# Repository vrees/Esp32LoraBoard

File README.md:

# Esp32LoraBoard
ESP32 board including Lora RFM95 module optimized for low power deep sleep operation. 

## Features:
* works with single LiFePo battery
* external peripheral (i2c bus, Oled, measurement resistors) can be switxched off by FET transistors
* Open Source. Feel free to modify in KiCad and create your own boards
* I2C bus is decoubled be levelshifters
* optional power supply circuit (solder if you don't want do use LiFePo battery supply)
* optional Rotary Encoder 
* there is no UART chip (like CP2104) onboard in order to save power. Board can be programmed by using a simple external USB-to-UART converter (5 Pins: Ground, RX, TX RTS, DTR)

[PCB](../master/kicad/images_V1.1/Esp32LoraBoard_Kicad_PCB_V1.1.png)

### Power consumption

#### Power on and idle 

After PowerOn without sending any Lora data

| Mode              | Current usage |
| ----------------- |:-------------:|
| Normal operation  | 28 mA         |

#### Deep Sleep 

Switched off all peripheral components and shutdown the RFM95W lora chip.

| Mode              | Current usage |
| ----------------- |:-------------:|
| Deep Sleep        | 26 uA         |

### Get Started

* Clone this project and open in platformio.

* Clone ttn-esp32 into lib subdir. Switch to branch dev to get it running. More info see https://github.com/manuelbl/ttn-esp32

* Following has to be changed under in ./lib/ttn-esp32 
Change following:

__src/lmic/config.h__
#define USE_ORIGINAL_AES

__src/aes/lmic_aes.c__
line 263:  u4_t t0, t1=0, t2, t3;

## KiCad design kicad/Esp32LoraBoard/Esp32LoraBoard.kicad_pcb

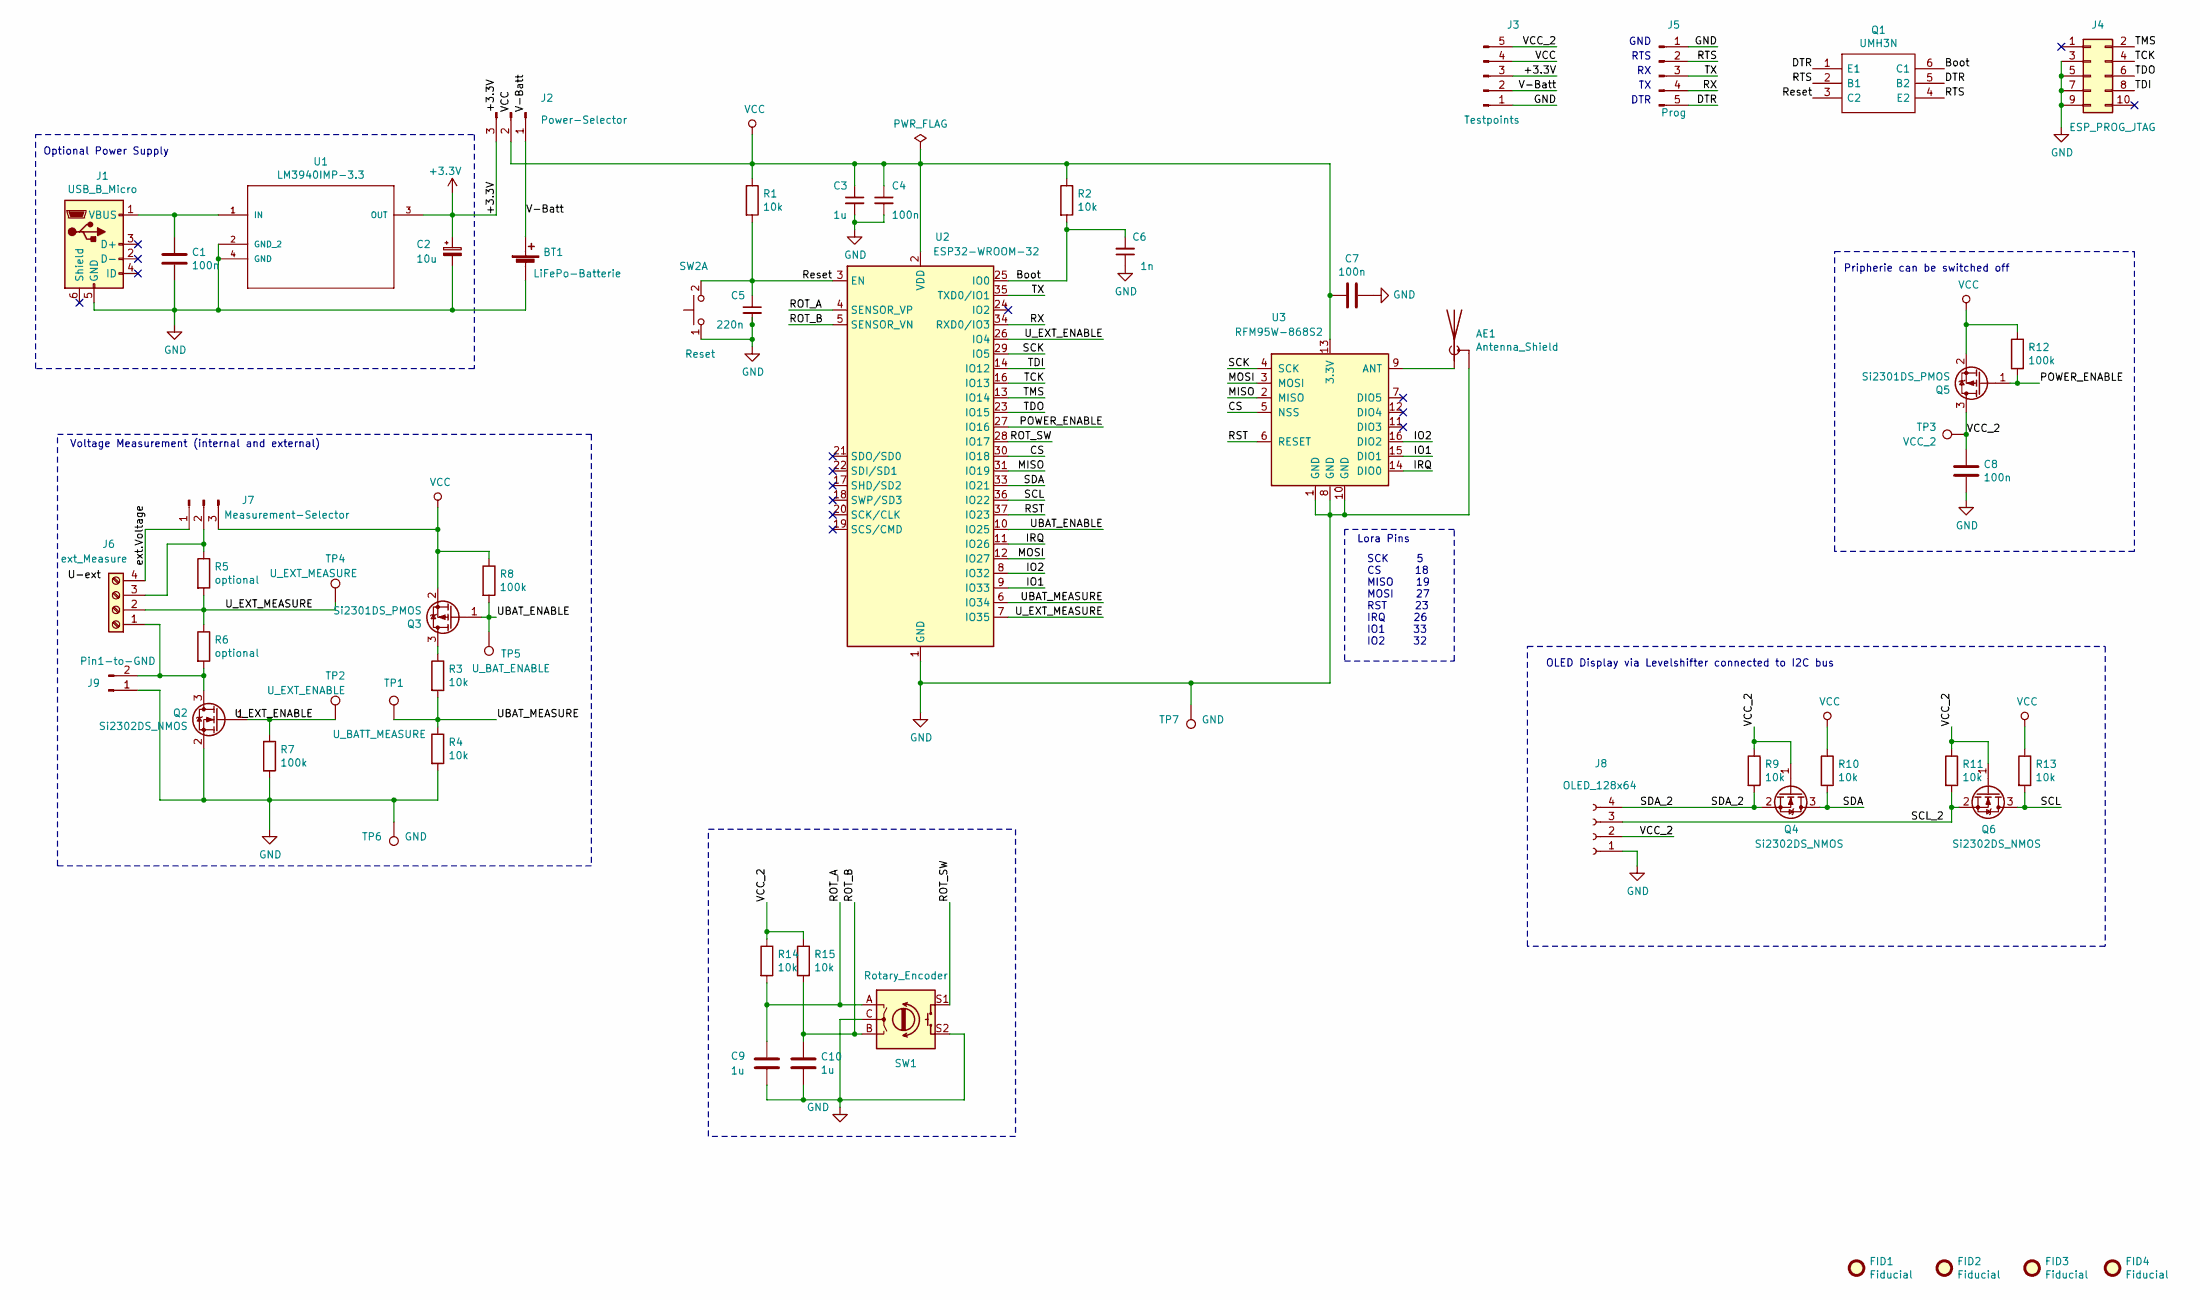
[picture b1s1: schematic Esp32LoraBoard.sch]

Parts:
AE1: Antenna_Shield; SMA_Samtec_SMA-J-P-H-ST-EM1_EdgeMount
BT1: LiFePo-Batterie; PhoenixContact_MSTBVA_2,5_2-G-5,08_1x02_P5.08mm_Vertical
C1, C4, C7, C8: 100n; C_1206_3216Metric_Pad1.42x1.75mm_HandSolder
C2: 10u; C_1206_3216Metric_Pad1.42x1.75mm_HandSolder
C3, C9, C10: 1u; C_1206_3216Metric_Pad1.42x1.75mm_HandSolder
C5: 220n; C_1206_3216Metric_Pad1.42x1.75mm_HandSolder
C6: 1n; C_1206_3216Metric_Pad1.42x1.75mm_HandSolder
FID1, FID2, FID3, FID4: Fiducial; Fiducial_0.75mm_Mask1.5mm
J1: USB_B_Micro; USB_Micro-B_GCT_USB3076-30-A
J2: Power-Selector; PinHeader_1x03_P2.54mm_Vertical
J3: Testpoints; PinHeader_1x05_P2.54mm_Vertical
J4: ESP_PROG_JTAG; PinHeader_2x05_P1.27mm_Vertical
J5: Prog; PinHeader_1x05_P2.54mm_Vertical
J6: ext_Measure; PhoenixContact_MSTBVA_2,5_4-G-5,08_1x04_P5.08mm_Vertical
J7: Measurement-Selector; PinHeader_1x03_P2.54mm_Vertical
J8: OLED_128x64; PinHeader_1x04_P2.54mm_Vertical
J9: Pin1-to-GND; PinHeader_1x02_P2.54mm_Vertical
Q1: UMH3N; SOT65P230X110-6N; Manufacturer_Part_Number UMH3N
Q2, Q4, Q6: Si2302DS_NMOS; TSOT-23_HandSoldering
Q3, Q5: Si2301DS_PMOS; TSOT-23_HandSoldering
R1, R2, R3, R4, R9, R10, R11, R13, R14, R15: 10k; R_1206_3216Metric_Pad1.42x1.75mm_HandSolder
R5, R6: optional; R_1206_3216Metric_Pad1.42x1.75mm_HandSolder
R7, R8, R12: 100k; R_1206_3216Metric_Pad1.42x1.75mm_HandSolder
SW1: Rotary_Encoder; RotaryEncoder_Alps_EC11E-Switch_Vertical_H20mm
SW2: Reset; SW_SPST_CK_RS282G05A3
TP1: U_BATT_MEASURE; PinHeader_1x01_P2.54mm_Vertical
TP2: U_EXT_ENABLE; PinHeader_1x01_P2.54mm_Vertical
TP3: VCC_2; PinHeader_1x01_P2.54mm_Vertical
TP4: U_EXT_MEASURE; PinHeader_1x01_P2.54mm_Vertical
TP5: U_BAT_ENABLE; PinHeader_1x01_P2.54mm_Vertical
TP6, TP7: GND; PinHeader_1x01_P2.54mm_Vertical
U1: LM3940IMP-3.3; SOT230P696X180-4N
U2: ESP32-WROOM-32
U3: RFM95W-868S2; HOPERF_RFM9XW_SMD

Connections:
+3V3: C2.1, J2.3, J3.3, U1.3 (OUT)
/Boot: C6.2, Q1.6 (C1), R2.2, U2.25 (IO0)
/CS: U2.30 (IO18), U3.5 (NSS)
/DTR: J5.5, Q1.1 (E1), Q1.5 (B2)
/IO1: U2.9 (IO33), U3.15 (DIO1)
/IO2: U2.8 (IO32), U3.16 (DIO2)
/IRQ: U2.11 (IO26), U3.14 (DIO0)
/MISO: U2.31 (IO19), U3.2 (MISO)
/MOSI: U2.12 (IO27), U3.3 (MOSI)
/POWER_ENABLE: Q5.1 (G), R12.2, U2.27 (IO16)
/ROT_A: C9.1, R14.2, SW1.A, U2.4 (SENSOR_VP)
/ROT_B: C10.1, R15.2, SW1.B, U2.5 (SENSOR_VN)
/ROT_SW: SW1.S1, U2.28 (IO17)
/RST: U2.37 (IO23), U3.6 (RESET)
/RTS: J5.2, Q1.2 (B1), Q1.4 (E2)
/RX: J5.4, U2.34 (RXD0/IO3)
/Reset: C5.1, Q1.3 (C2), R1.2, SW2.2 (D), U2.3 (EN)
/SCK: U2.29 (IO5), U3.4 (SCK)
/SCL: Q6.3 (D), R13.2, U2.36 (IO22)
/SCL_2: J8.3, Q6.2 (S), R11.2
/SDA: Q4.3 (D), R10.2, U2.33 (IO21)
/SDA_2: J8.4, Q4.2 (S), R9.2
/TCK: J4.4, U2.16 (IO13)
/TDI: J4.8, U2.14 (IO12)
/TDO: J4.6, U2.23 (IO15)
/TMS: J4.2, U2.13 (IO14)
/TX: J5.3, U2.35 (TXD0/IO1)
/UBAT_ENABLE: Q3.1 (G), R8.2, TP5.1, U2.10 (IO25)
/UBAT_MEASURE: R3.2, R4.1, TP1.1, U2.6 (IO34)
/U_EXT_ENABLE: Q2.1 (G), R7.1, TP2.1, U2.26 (IO4)
/U_EXT_MEASURE: J6.2, R5.2, R6.1, TP4.1, U2.7 (IO35)
/V-Batt: BT1.1 (+), J2.1, J3.2
/VCC_2: C8.1, J3.5, J8.2, Q4.1 (G), Q5.3 (D), Q6.1 (G), R9.1, R11.1, R14.1, R15.1, TP3.1
/ext.Voltage: J6.4, J7.1
GND: AE1.2 (Shield), BT1.2 (-), C1.2, C2.2, C3.2, C4.2, C5.2, C6.1, C7.1, C8.2, C9.2, C10.2, J1.5 (GND), J3.1, J4.3, J4.5, J4.7, J4.9, J5.1, J8.1, J9.1, Q2.2 (S), R4.2, R7.2, SW1.C, SW1.S2, SW2.1 (C), TP6.1, TP7.1, U1.2 (GND_2), U1.4 (GND), U2.1 (GND), U2.15 (GND), U2.38 (GND), U2.39 (GND), U3.1 (GND), U3.8 (GND), U3.10 (GND)
unnamed: AE1.1 (A), U3.9 (ANT)
unnamed: C1.1, J1.1 (VBUS), U1.1 (IN)
unnamed: J6.1, J9.2, Q2.3 (D), R6.2
unnamed: J6.3, J7.2, R5.1
unnamed: Q3.3 (D), R3.1
VCC: C3.1, C4.1, C7.2, J2.2, J3.4, J7.3, Q3.2 (S), Q5.2 (S), R1.1, R2.1, R8.1, R10.1, R12.1, R13.1, U2.2 (VDD), U3.13 (3.3V)

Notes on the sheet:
SCK 5 CS 18 MISO 19 MOSI 27 RST 23 IRQ 26 IO1 33 IO2 32
DTR
RTS
GND
Lora Pins
OLED Display via Levelshifter connected to I2C bus
Pripherie can be switched off
Voltage Measurement (internal and external)
Optional Power Supply

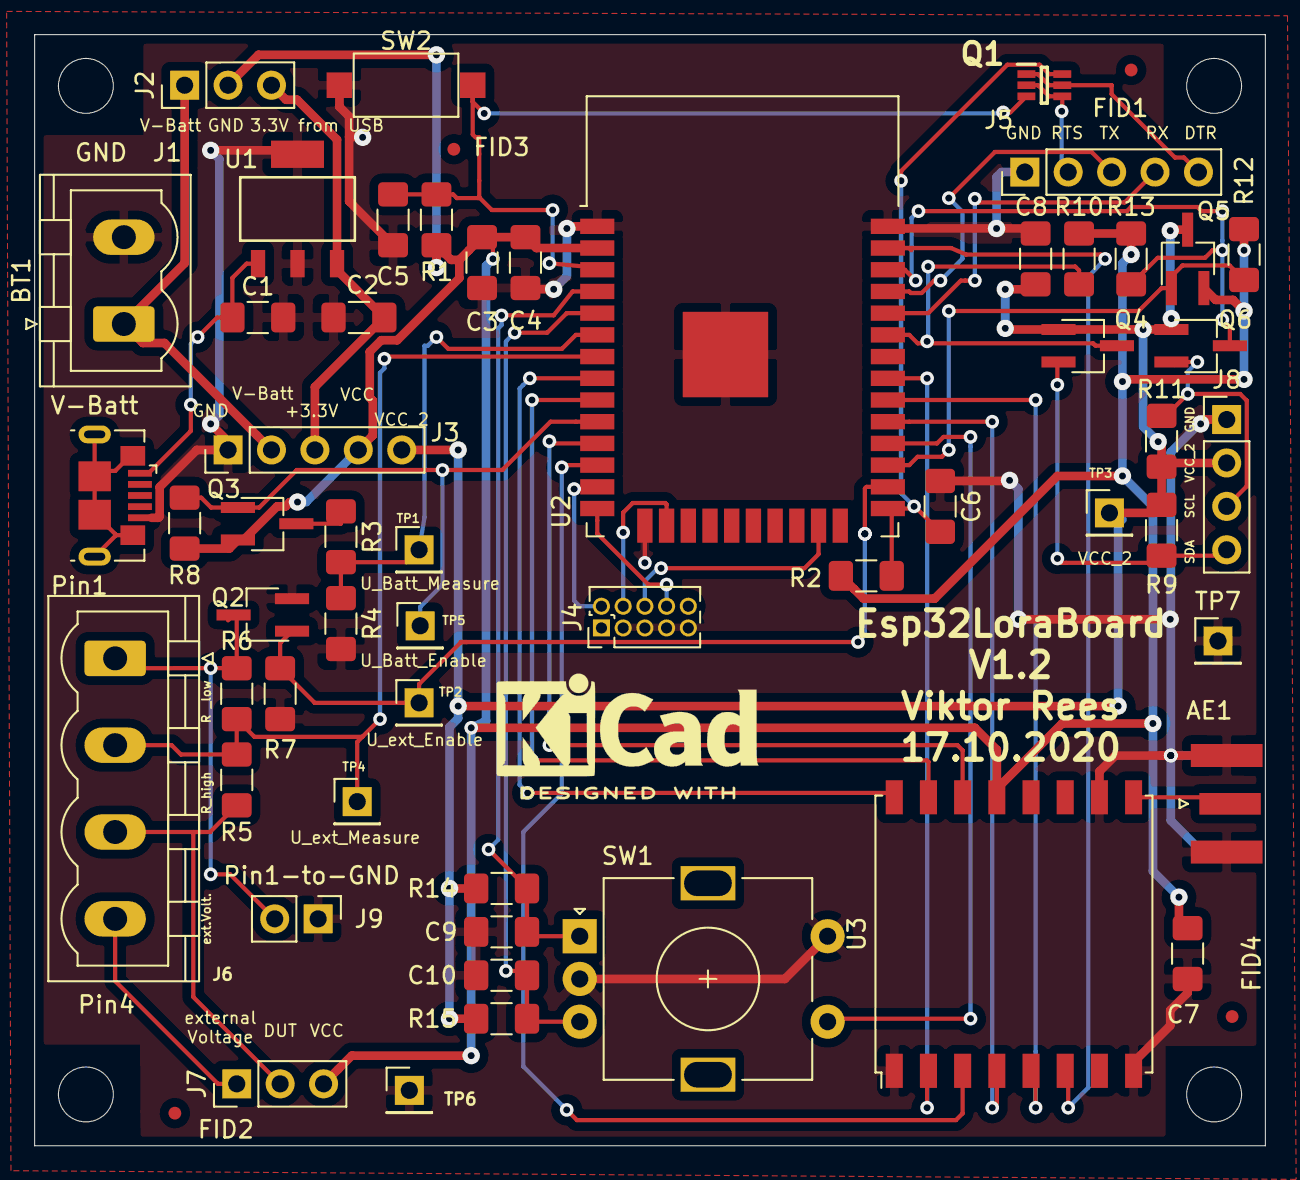
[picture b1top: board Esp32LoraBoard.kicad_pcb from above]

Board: 2 copper layers, 72.0 x 65.0 mm, 58 parts (0 on the bottom side), 41 nets.

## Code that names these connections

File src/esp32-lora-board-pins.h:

#ifndef _ESP32_LORA_BOARD_PINS_H_
#define _ESP32_LORA_BOARD_PINS_H_

// Pins for LORA chip SPI interface, reset line and interrupt lines (compatible TTGO LoRa32 V2.1.6)
// #define LORA_SCK  (5) 
// #define LORA_CS   (18)
// #define LORA_MISO (19)
// #define LORA_MOSI (27)
// #define LORA_RST  (23)
// #define LORA_IRQ  (26)
// #define LORA_IO1  (33)
// #define LORA_IO2  (32)

// Pins and other resources
#define TTN_SPI_HOST      HSPI_HOST
#define TTN_SPI_DMA_CHAN  1
#define TTN_PIN_SPI_SCLK  5
#define TTN_PIN_SPI_MOSI  27
#define TTN_PIN_SPI_MISO  19
#define TTN_PIN_NSS       18
#define TTN_PIN_RXTX      TTN_NOT_CONNECTED
#define TTN_PIN_RST       23
#define TTN_PIN_DIO0      26
#define TTN_PIN_DIO1      33


// JTAG ESP-Programmer
#define JTAG_TDI        (12)
#define JTAG_TCK        (13)
#define JTAG_TMS        (14)
#define JTAG_TDO        (15)

// Control Pins
#define POWER_ENABLE    (16)
#define U_EXT_ENABLE    (4)
#define U_EXT_MEASURE   (35)    // ADC1_CHANNEL_7
#define U_BAT_ENABLE     (25)
#define U_BAT_MEASURE    (34)   // ADC1_CHANNEL_6

// IO
#define ROTARY_SWITCH   (17)
#define ROTARY_A        (36)
#define ROTARY_B        (39)
#define RESERVED        (2)

// I2C Bus
#define I2C_SDA         (21)
#define I2C_SCL         (22)

// Serial Connection
#define TXDO            (1)
#define RXDO            (3)

#endif

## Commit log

2020-05-05 initial dummy commit
2020-05-05 added kicad files
2020-05-05 adde schema and images
2020-05-05 added deep sleep logic
2020-05-26 backup
2020-05-26 Working Verion using esp-idf
2020-05-26 Power FETs disabled during startup
2020-05-26 readme changed
2020-05-28 try to integrate ttn-esp32
2020-05-29 fix ttn-esp32 problems
2020-05-29 Images added
2020-05-29 Doc changed
2020-08-22 auto version update
2020-08-28 added voltage measurment
2020-08-28 updated ttn-esp32
2020-08-30 ttn message changed
2020-08-30 show tx/rx/rssi
2020-08-30 use Mac address for Dev EUI
2020-09-01 decode as 2 bytes
2020-09-02 Cayenne added
2020-10-17 not working yet
2020-10-18 new PCB Version V1.2
2020-11-08 print wakeup reason
2020-11-08 wakeup on low water lever
2020-11-08 ifndef USE_GPIO35_DIGITAL_IN
2020-11-08 linker error - ld returned 1 exit status Not working yet
2020-11-09 wakeup by level change
2020-11-11 3.3Volt Measurement by PolynomInterpolation
2020-11-21 Doku added
2020-12-19 code overtaken from project wasserstand-harry-b
2020-12-20 first running version usin u8g2
2020-12-20 extracted display.c / .h
2020-12-21 Added display messages
2020-12-21 added bootCount to Payload
2020-12-26 changed display message
2021-01-08 Antennen Messungen hinzugefügt
2021-11-01 sdkconfig
2021-11-01 HT7833 added
